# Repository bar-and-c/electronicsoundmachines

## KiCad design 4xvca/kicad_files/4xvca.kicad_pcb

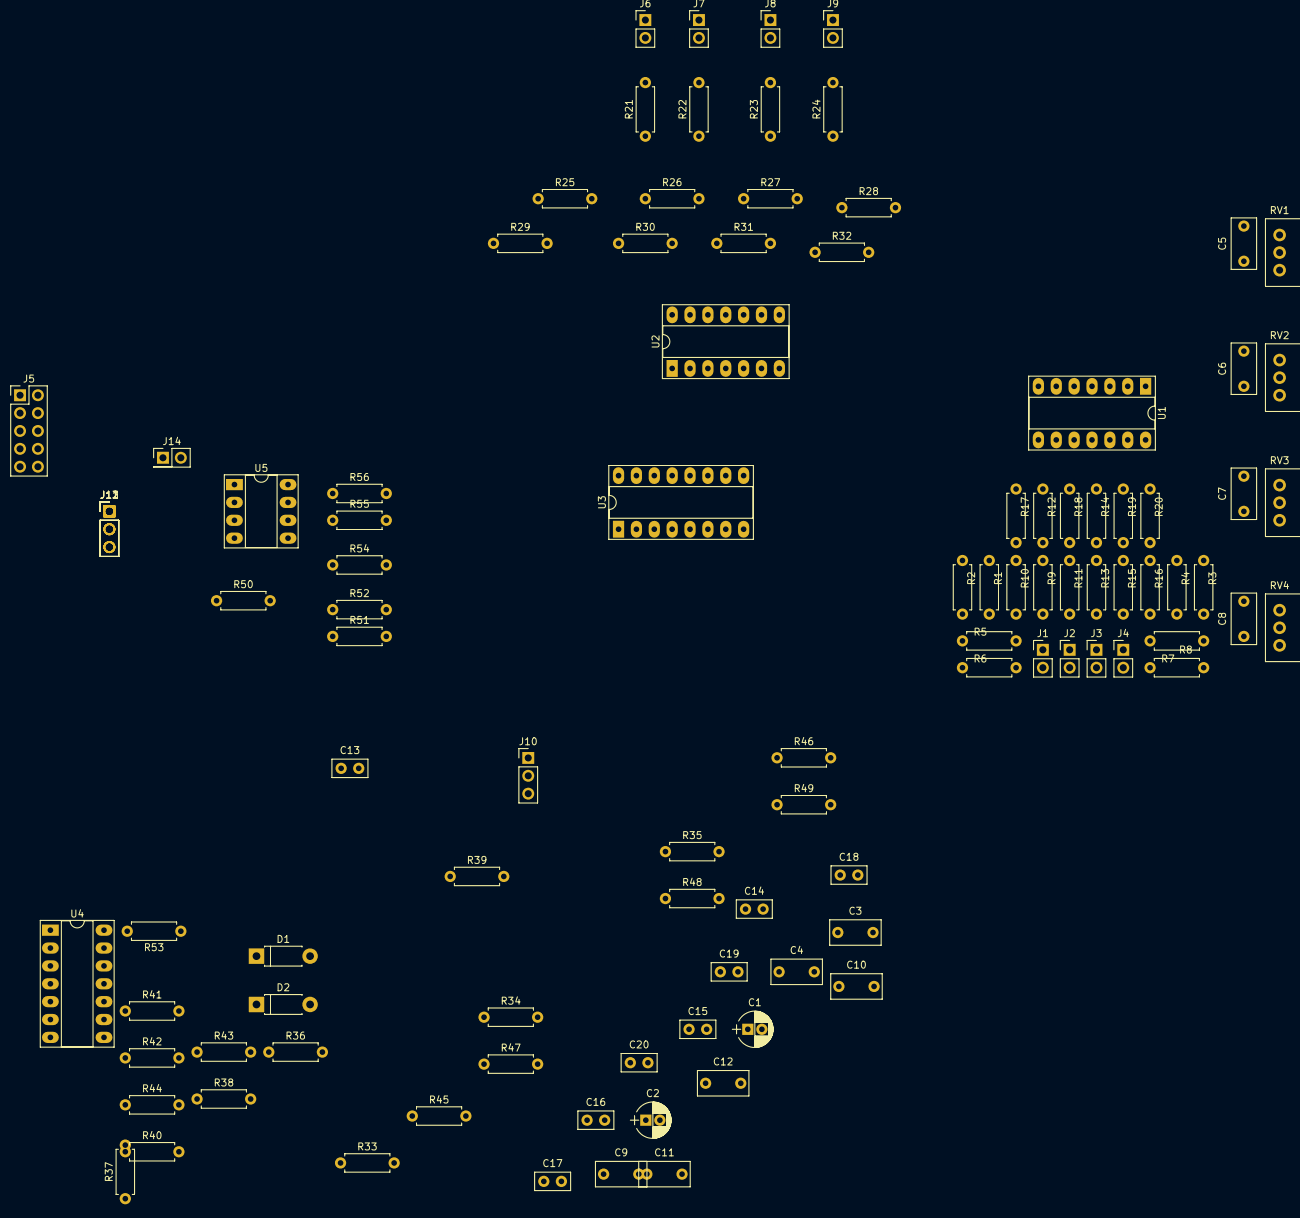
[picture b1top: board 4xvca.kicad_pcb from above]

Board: 2 copper layers, 101 parts (0 on the bottom side), 63 nets, no tracks yet.

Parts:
C1, C2: 10uF; CP_Radial_D5.0mm_P2.00mm
C3, C4, C5, C6, C7, C8, C9, C10, C11, C12: 100nF; C_Rect_L7.2mm_W3.5mm_P5.00mm_FKS2_FKP2_MKS2_MKP2
C13, C14, C15, C16: 560pF; C_Disc_D5.0mm_W2.5mm_P2.50mm
C17, C18, C19, C20: 100pF; C_Disc_D5.0mm_W2.5mm_P2.50mm
D1, D2: 1N4001; D_DO-41_SOD81_P7.62mm_Horizontal
J1: CV_1; Pin_Header_Straight_1x02_Pitch2.54mm
J2: CV_2; Pin_Header_Straight_1x02_Pitch2.54mm
J3: CV_3; Pin_Header_Straight_1x02_Pitch2.54mm
J4: CV_4; Pin_Header_Straight_1x02_Pitch2.54mm
J5: EUROPOWER; Pin_Header_Straight_2x05_Pitch2.54mm
J6: IN_1; Pin_Header_Straight_1x02_Pitch2.54mm
J7: IN_2; Pin_Header_Straight_1x02_Pitch2.54mm
J8: IN_3; Pin_Header_Straight_1x02_Pitch2.54mm
J9: IN_4; Pin_Header_Straight_1x02_Pitch2.54mm
J10: OUT_1; Pin_Header_Straight_1x03_Pitch2.54mm
J11: OUT_2; Pin_Header_Straight_1x03_Pitch2.54mm
J12: OUT_3; Pin_Header_Straight_1x03_Pitch2.54mm
J13: OUT_4; Pin_Header_Straight_1x03_Pitch2.54mm
J14: MIX_OUT; Pin_Header_Straight_2x01_Pitch2.54mm
R1, R2, R3, R4: 15k; R_Axial_DIN0207_L6.3mm_D2.5mm_P7.62mm_Horizontal
R5, R6, R7, R8: 12k; R_Axial_DIN0207_L6.3mm_D2.5mm_P7.62mm_Horizontal
R9, R10, R11, R12, R13, R14, R15, R16: 62k; R_Axial_DIN0207_L6.3mm_D2.5mm_P7.62mm_Horizontal
R17, R18, R19, R20, R21, R22, R23, R24, R25, R26, R27, R28, R40, R43, R44, R49, R54: 100k; R_Axial_DIN0207_L6.3mm_D2.5mm_P7.62mm_Horizontal
R29, R30, R31, R32, R38, R39, R41, R42: 30k; R_Axial_DIN0207_L6.3mm_D2.5mm_P7.62mm_Horizontal
R33, R34, R35, R36: 500; R_Axial_DIN0207_L6.3mm_D2.5mm_P7.62mm_Horizontal
R37: 7.5k; R_Axial_DIN0207_L6.3mm_D2.5mm_P7.62mm_Horizontal
R45, R46, R47, R48, R55: 1k; R_Axial_DIN0207_L6.3mm_D2.5mm_P7.62mm_Horizontal
R50, R51, R52, R53, R56: 100; R_Axial_DIN0207_L6.3mm_D2.5mm_P7.62mm_Horizontal
RV1, RV2, RV3, RV4: 100k; Potentiometer_Alps_RK09Y_Vertical
U1, U2, U4: TL074; DIP-14_W7.62mm_Socket_LongPads
U3: V2164M; DIP-16_W7.62mm_Socket_LongPads
U5: TL071; DIP-8_W7.62mm_Socket_LongPads

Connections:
+12V: C1.1, C3.1, C9.1, C11.1, D1.1, J5.9, J5.10, R37.1, U1.4, U2.4, U3.16, U4.4, U5.7
-12V: C2.2, C4.2, C10.2, C12.2, D2.2, J5.1, J5.2, R1.2, R2.2, R3.2, R4.2, U1.11, U2.11, U3.9, U4.11, U5.4
GND: C1.2, C2.1, C3.2, C4.1, C5.2, C6.2, C7.2, C8.2, C9.2, C10.1, C11.2, C12.1, C13.2, C14.2, C15.2, C16.2, D1.2, D2.1, J1.2, J2.2, J3.2, J4.2, J5.3, J5.4, J5.5, J5.6, J5.7, J5.8, J6.2, J7.2, J8.2, J9.2, J10.2, J11.2, J12.2, J13.2, J14.2, R5.1, R6.1, R7.1, R8.1, R45.2, R46.2, R47.2, R48.2, R55.2, RV1.3, RV2.3, RV3.3, RV4.3, U1.3, U1.5, U1.10, U1.12, U2.3, U2.5, U2.10, U2.12, U3.8, U4.3, U4.5, U4.10, U4.12, U5.3
unnamed: C5.1, RV1.2, U3.3
unnamed: C6.1, RV2.2, U3.6
unnamed: C7.1, RV3.2, U3.11
unnamed: C8.1, RV4.2, U3.14
unnamed: C13.1, R33.2
unnamed: C14.1, R34.2
unnamed: C15.1, R35.2
unnamed: C16.1, R36.2
unnamed: C17.1, R38.1, R45.1, R50.2, U4.1
unnamed: C17.2, R38.2, U3.4, U4.2
unnamed: C18.1, R39.1, R47.1, R52.2, U4.7
unnamed: C18.2, R39.2, U3.12, U4.6
unnamed: C19.1, R41.1, R46.1, R51.2, U4.8
unnamed: C19.2, R41.2, U3.5, U4.9
unnamed: C20.1, R42.1, R48.1, R53.2, U4.14
unnamed: C20.2, R42.2, U3.13, U4.13
unnamed: J1.1, R9.2
unnamed: J2.1, R11.2
unnamed: J3.1, R13.2
unnamed: J4.1, R15.2
unnamed: J6.1, R21.2
unnamed: J7.1, R22.2
unnamed: J8.1, R23.2
unnamed: J9.1, R24.2
unnamed: J10.1, R50.1
unnamed: J10.3, R40.1
unnamed: J11.1, R51.1
unnamed: J11.3, R43.1
unnamed: J12.1, R52.1
unnamed: J12.3, R44.1
unnamed: J13.1, R53.1
unnamed: J13.3, R49.1
unnamed: J14.1, R56.1
unnamed: R1.1, R5.2, R10.2
unnamed: R9.1, R10.1, R17.2, U1.2
unnamed: R11.1, R12.1, R18.2, U1.6
unnamed: R2.1, R6.2, R12.2
unnamed: R13.1, R14.1, R19.2, U1.9
unnamed: R3.1, R7.2, R14.2
unnamed: R15.1, R16.1, R20.2, U1.13
unnamed: R4.1, R8.2, R16.2
unnamed: R17.1, RV1.1, U1.1
unnamed: R18.1, RV2.1, U1.7
unnamed: R19.1, RV3.1, U1.8
unnamed: R20.1, RV4.1, U1.14
unnamed: R21.1, R25.2, U2.2
unnamed: R22.1, R26.2, U2.6
unnamed: R23.1, R27.2, U2.9
unnamed: R24.1, R28.2, U2.13
unnamed: R25.1, R29.2, U2.1
unnamed: R26.1, R30.2, U2.7
unnamed: R27.1, R31.2, U2.8
unnamed: R28.1, R32.2, U2.14
unnamed: R29.1, R33.1, U3.2
unnamed: R30.1, R34.1, U3.7
unnamed: R31.1, R35.1, U3.10
unnamed: R32.1, R36.1, U3.15
unnamed: R37.2, U3.1
unnamed: R40.2, R43.2, R44.2, R49.2, R54.2, U5.2
unnamed: R54.1, R55.1, R56.2, U5.6

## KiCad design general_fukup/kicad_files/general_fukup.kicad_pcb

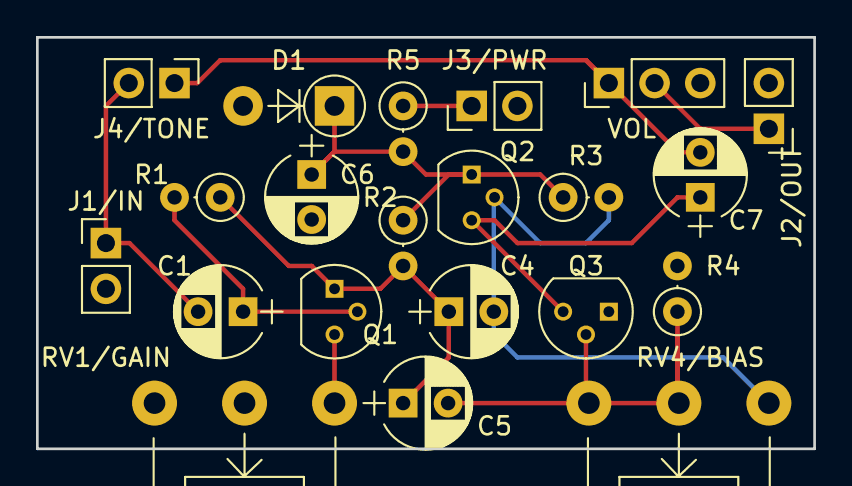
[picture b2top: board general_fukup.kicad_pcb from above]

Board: 2 copper layers, 43.2 x 22.9 mm, 21 parts (0 on the bottom side), 12 nets.

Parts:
C1: 100uF; CP_Radial_D5.0mm_P2.50mm
C4, C5, C7: 4.7 uF; CP_Radial_D5.0mm_P2.50mm
C6: 22 uF; CP_Radial_D5.0mm_P2.50mm
D1: 1N4001; D_DO-41_SOD81_P5.08mm_Vertical_AnodeUp
J1/IN: INPUT; Pin_Header_Straight_1x02_Pitch2.54mm
J2/OUT: OUTPUT; Pin_Header_Straight_1x02_Pitch2.54mm
J3/PWR: POWER; Pin_Header_Straight_1x02_Pitch2.54mm
J4/TONE: TONE; Pin_Header_Straight_1x02_Pitch2.54mm
Q1, Q2: BC337; TO-92_Molded_Narrow
Q3: BC327; TO-92_Molded_Narrow
R1: 1M; R_Axial_DIN0207_L6.3mm_D2.5mm_P2.54mm_Vertical
R2: 10k; R_Axial_DIN0207_L6.3mm_D2.5mm_P2.54mm_Vertical
R3, R4: 47k; R_Axial_DIN0207_L6.3mm_D2.5mm_P2.54mm_Vertical
R5: 150; R_Axial_DIN0207_L6.3mm_D2.5mm_P2.54mm_Vertical
RV1/GAIN, RV4/BIAS: 10k lin; Potentiometer_WirePads
VOL: 100k log; Pin_Header_Straight_1x03_Pitch2.54mm

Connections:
+9V: J3/PWR.1, R5.1
GND: C6.2, D1.2, J1/IN.2, J2/OUT.2, J3/PWR.2, Q3.1, R4.2, RV1/GAIN.2, RV1/GAIN.3, VOL.3
unnamed: C1.1, Q1.2, R1.2
unnamed: C1.2, J1/IN.1, J4/TONE.2
unnamed: C4.1, C5.1, Q1.1, R1.1, R2.2
unnamed: C4.2, Q2.2, R3.2, RV4/BIAS.1
unnamed: C5.2, Q3.2, R4.1, RV4/BIAS.2, RV4/BIAS.3
unnamed: C6.1, D1.1, Q2.1, R2.1, R3.1, R5.2
unnamed: C7.1, Q2.3, Q3.3
unnamed: C7.2, J4/TONE.1, VOL.1
unnamed: J2/OUT.1, VOL.2
unnamed: Q1.3, RV1/GAIN.1

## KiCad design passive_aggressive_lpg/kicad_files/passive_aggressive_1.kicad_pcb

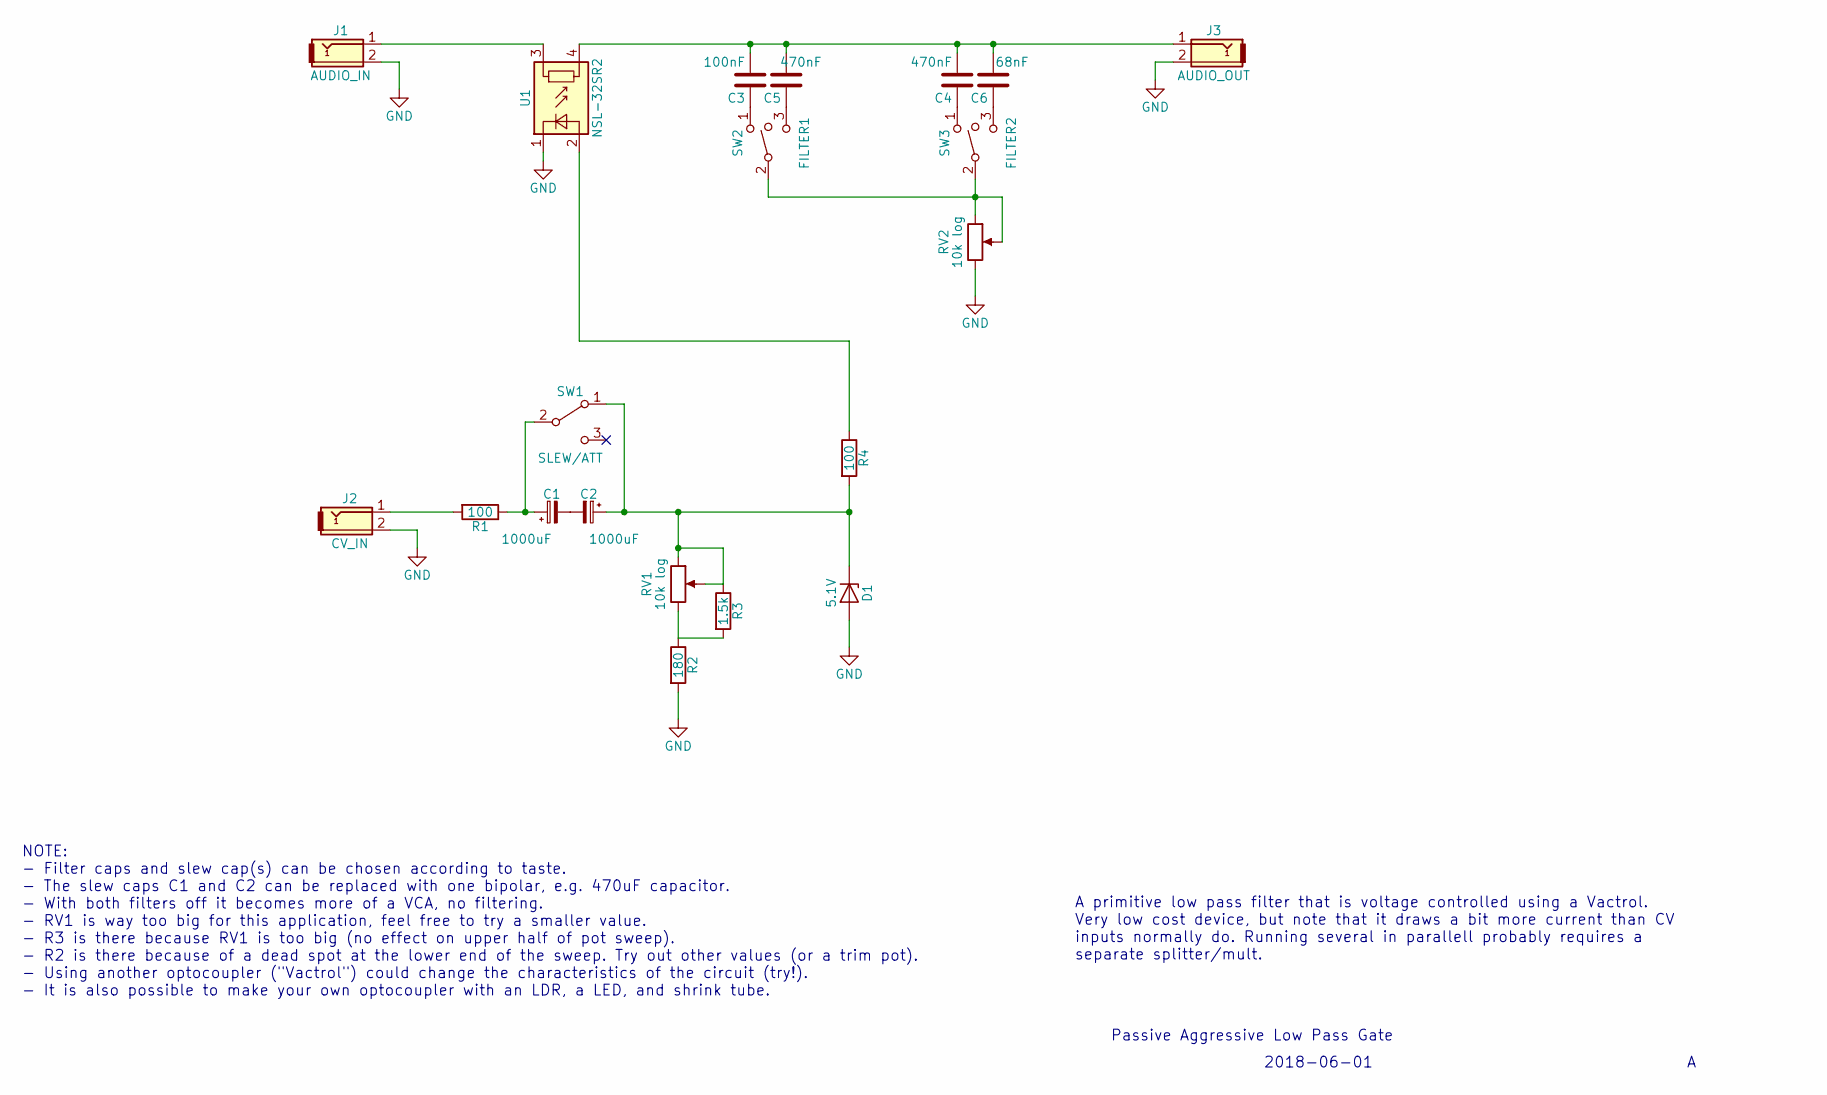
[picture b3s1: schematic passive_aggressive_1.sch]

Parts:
C1, C2: 1000uF; CP_Radial_D10.0mm_P5.00mm
C3: 100nF; C_Rect_L7.2mm_W3.5mm_P5.00mm_FKS2_FKP2_MKS2_MKP2
C4, C5: 470nF; C_Rect_L7.2mm_W3.5mm_P5.00mm_FKS2_FKP2_MKS2_MKP2
C6: 68nF; C_Rect_L7.2mm_W3.5mm_P5.00mm_FKS2_FKP2_MKS2_MKP2
D1: 5.1V; D_DO-35_SOD27_P7.62mm_Horizontal
J1: AUDIO_IN; Pin_Header_Straight_1x02_Pitch2.54mm
J2: CV_IN; Pin_Header_Straight_1x02_Pitch2.54mm
J3: AUDIO_OUT; Pin_Header_Straight_1x02_Pitch2.54mm
R1, R4: 100; R_Axial_DIN0207_L6.3mm_D2.5mm_P7.62mm_Horizontal
R2: 180; R_Axial_DIN0207_L6.3mm_D2.5mm_P7.62mm_Horizontal
R3: 1.5k; R_Axial_DIN0207_L6.3mm_D2.5mm_P7.62mm_Horizontal
RV1, RV2: 10k log; Potentiometer_Alps_RK097_Single_Vertical
SW1: SLEW/ATT; Pin_Header_Straight_1x02_Pitch2.54mm
SW2: FILTER1; Pin_Header_Straight_1x03_Pitch2.54mm
SW3: FILTER2; Pin_Header_Straight_1x03_Pitch2.54mm
U1: NSL-32SR2; Optoisolator_VTL5C

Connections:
GND: D1.2 (A), J1.2, J2.2, J3.2, R2.2, RV2.3, U1.1 (-)
unnamed: C1.1, R1.1, SW1.2 (B)
unnamed: C1.2, C2.2
unnamed: C2.1, D1.1 (K), R3.1, R4.2, RV1.1, RV1.2, SW1.1 (A)
unnamed: C3.1, SW2.1
unnamed: C3.2, C4.2, C5.2, C6.2, J3.1, U1.4
unnamed: C4.1, SW3.1
unnamed: C5.1, SW2.3
unnamed: C6.1, SW3.3
unnamed: J1.1, U1.3
unnamed: J2.1, R1.2
unnamed: R2.1, R3.2, RV1.3
unnamed: R4.1, U1.2 (+)
unnamed: RV2.1, RV2.2, SW2.2, SW3.2

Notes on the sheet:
Passive Aggressive Low Pass Gate
2018-06-01
NOTE: - Filter caps and slew cap(s) can be chosen according to taste. - The slew caps C1 and C2 can be replaced with one bipolar, e.g. 470uF capacitor. - With both filters off it becomes more of a VCA, no filtering. - RV1 is way too big for this application, feel free to try a smaller value. - R3 i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
A primitive low pass filter that is voltage controlled using a Vactrol. Very low cost device, but note that it draws a bit more current than CV inputs normally do. Running several in parallell probably requires a separate splitter/mult.

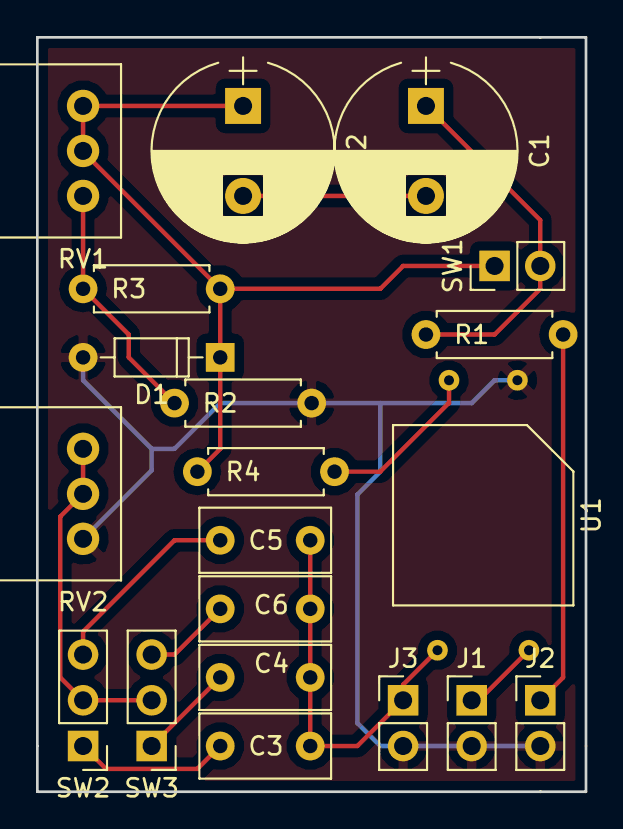
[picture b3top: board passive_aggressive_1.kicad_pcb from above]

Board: 2 copper layers, 30.5 x 41.9 mm, 20 parts (0 on the bottom side), 14 nets.

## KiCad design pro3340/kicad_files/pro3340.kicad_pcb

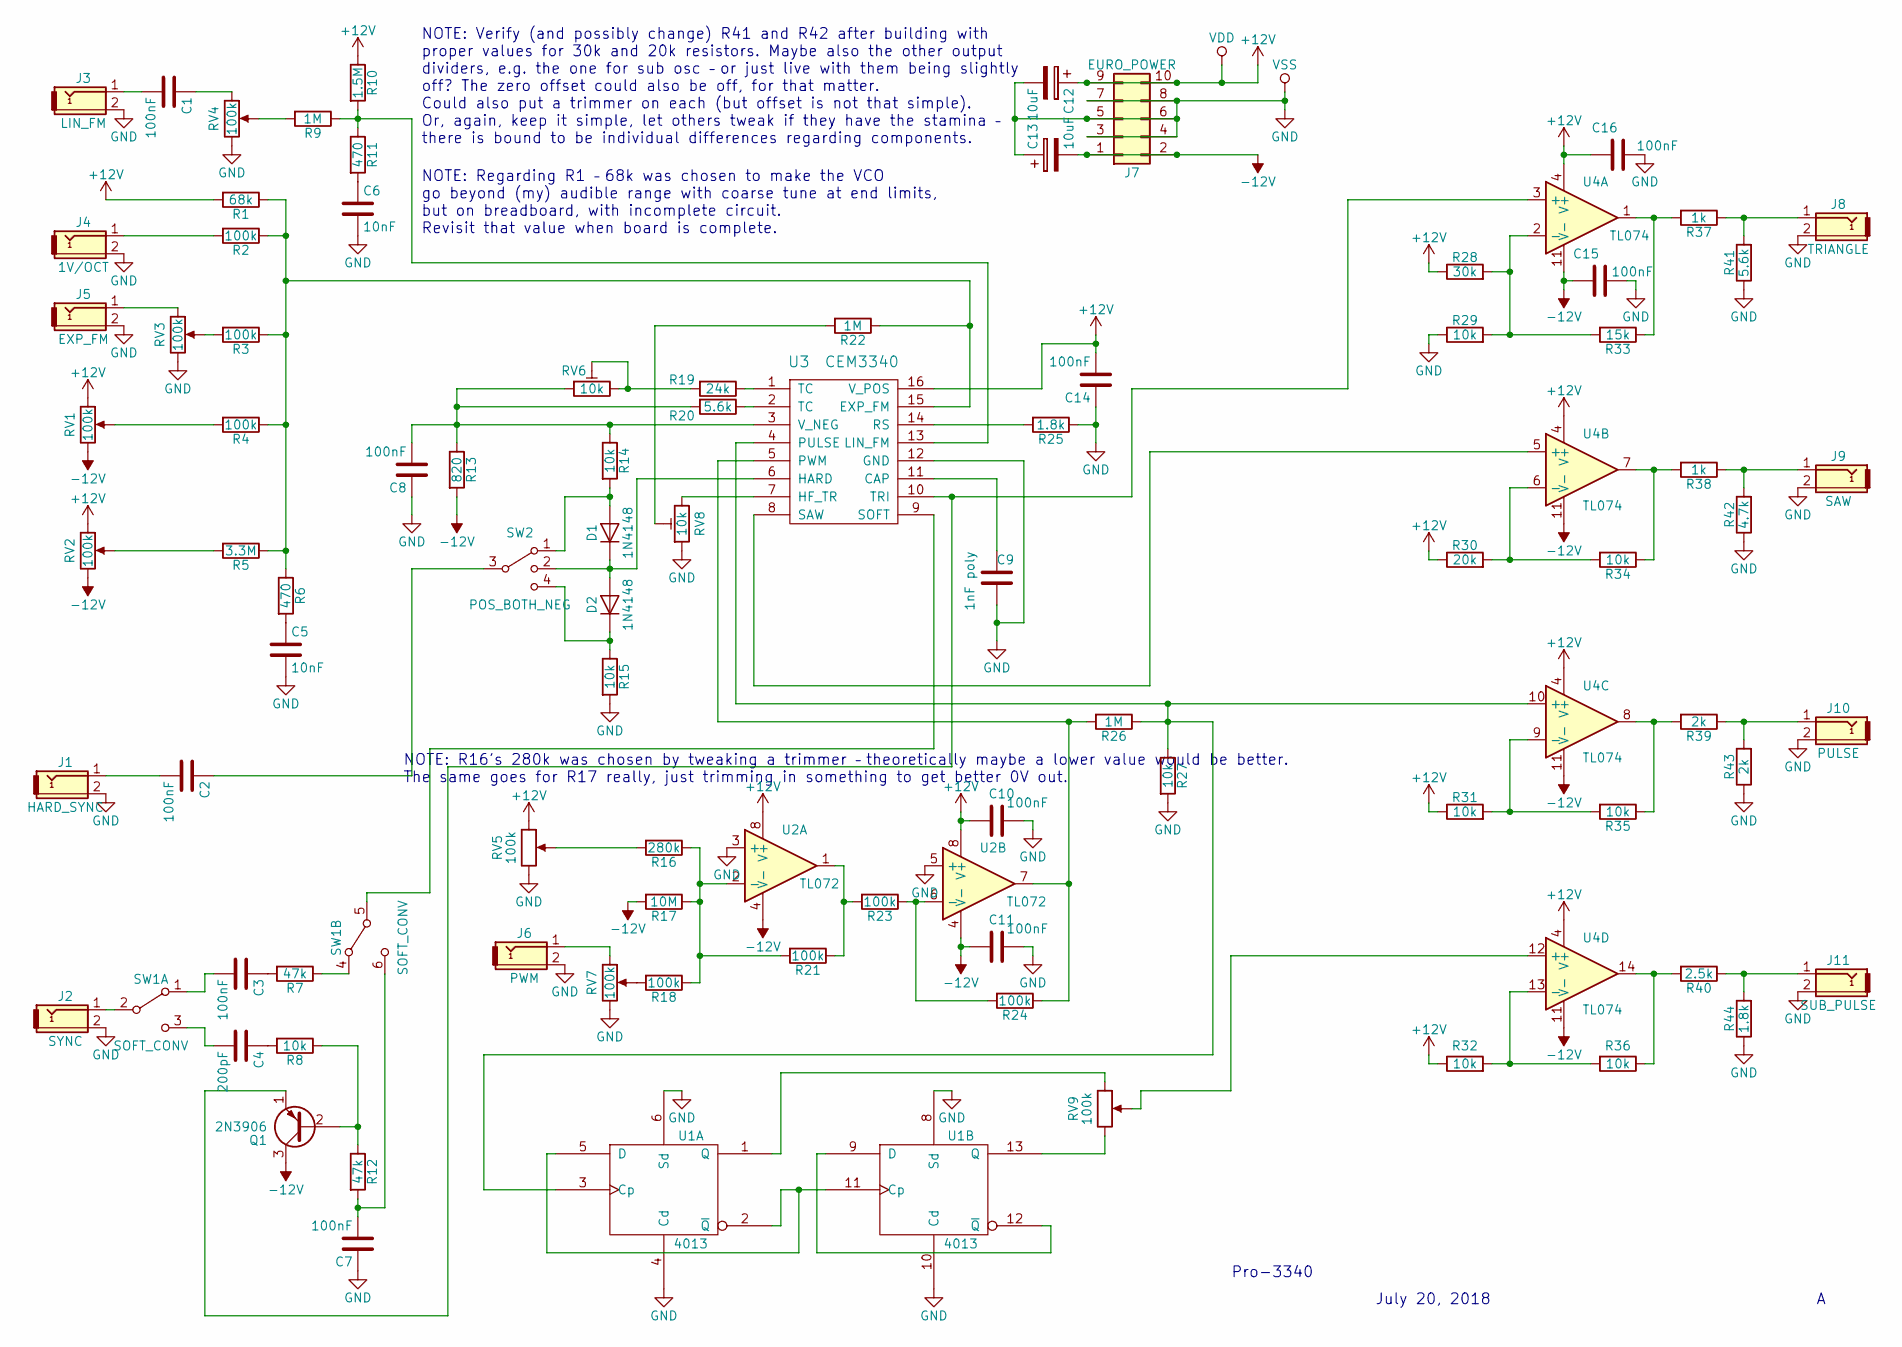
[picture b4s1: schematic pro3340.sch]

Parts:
C1, C2, C3, C7, C8, C10, C11, C14, C15, C16: 100nF; C_Rect_L7.0mm_W3.5mm_P5.00mm
C4: 200pF; C_Rect_L7.0mm_W3.5mm_P5.00mm
C5, C6: 10nF; C_Rect_L7.0mm_W3.5mm_P5.00mm
C9: 1nF poly; C_Axial_L12.0mm_D6.5mm_P15.00mm_Horizontal
C12, C13: 10uF; CP_Radial_D5.0mm_P2.50mm
D1, D2: 1N4148; D_DO-35_SOD27_P7.62mm_Horizontal
J1: HARD_SYNC; Pin_Header_Straight_1x02_Pitch2.54mm
J2: SYNC; Pin_Header_Straight_1x02_Pitch2.54mm
J3: LIN_FM; Pin_Header_Straight_1x02_Pitch2.54mm
J4: 1V/OCT; Pin_Header_Straight_1x02_Pitch2.54mm
J5: EXP_FM; Pin_Header_Straight_1x02_Pitch2.54mm
J6: PWM; Pin_Header_Straight_1x02_Pitch2.54mm
J7: EURO_POWER; Pin_Header_Straight_2x05_Pitch2.54mm
J8: TRIANGLE; Pin_Header_Straight_1x02_Pitch2.54mm
J9: SAW; Pin_Header_Straight_1x02_Pitch2.54mm
J10: PULSE; Pin_Header_Straight_1x02_Pitch2.54mm
J11: SUB_PULSE; Pin_Header_Straight_1x02_Pitch2.54mm
Q1: 2N3906; TO-92_Inline_Wide
R1: 68k; R_Axial_DIN0207_L6.3mm_D2.5mm_P7.62mm_Horizontal
R2, R3, R4, R18, R21, R23, R24: 100k; R_Axial_DIN0207_L6.3mm_D2.5mm_P7.62mm_Horizontal
R5: 3.3M; R_Axial_DIN0207_L6.3mm_D2.5mm_P7.62mm_Horizontal
R6, R11: 470; R_Axial_DIN0207_L6.3mm_D2.5mm_P7.62mm_Horizontal
R7, R12: 47k; R_Axial_DIN0207_L6.3mm_D2.5mm_P7.62mm_Horizontal
R8, R14, R15, R27, R29, R31, R32, R34, R35, R36: 10k; R_Axial_DIN0207_L6.3mm_D2.5mm_P7.62mm_Horizontal
R9, R22, R26: 1M; R_Axial_DIN0207_L6.3mm_D2.5mm_P7.62mm_Horizontal
R10: 1.5M; R_Axial_DIN0207_L6.3mm_D2.5mm_P7.62mm_Horizontal
R13: 820; R_Axial_DIN0207_L6.3mm_D2.5mm_P7.62mm_Horizontal
R16: 280k; R_Axial_DIN0207_L6.3mm_D2.5mm_P7.62mm_Horizontal
R17: 10M; R_Axial_DIN0207_L6.3mm_D2.5mm_P7.62mm_Horizontal
R19: 24k; R_Axial_DIN0207_L6.3mm_D2.5mm_P7.62mm_Horizontal
R20, R41: 5.6k; R_Axial_DIN0207_L6.3mm_D2.5mm_P7.62mm_Horizontal
R25, R44: 1.8k; R_Axial_DIN0207_L6.3mm_D2.5mm_P7.62mm_Horizontal
R28: 30k; R_Axial_DIN0207_L6.3mm_D2.5mm_P7.62mm_Horizontal
R30: 20k; R_Axial_DIN0207_L6.3mm_D2.5mm_P7.62mm_Horizontal
R33: 15k; R_Axial_DIN0207_L6.3mm_D2.5mm_P7.62mm_Horizontal
R37, R38: 1k; R_Axial_DIN0207_L6.3mm_D2.5mm_P7.62mm_Horizontal
R39, R43: 2k; R_Axial_DIN0207_L6.3mm_D2.5mm_P7.62mm_Horizontal
R40: 2.5k; R_Axial_DIN0207_L6.3mm_D2.5mm_P7.62mm_Horizontal
R42: 4.7k; R_Axial_DIN0207_L6.3mm_D2.5mm_P7.62mm_Horizontal
RV1, RV2, RV3, RV4, RV5, RV7: 100k; Potentiometer_Alps_RK09Y_Vertical
RV6, RV8: 10k; Potentiometer_Trimmer_Bourns_3266Y
RV9: 100k; Pin_Header_Straight_1x03_Pitch2.54mm
SW1: SOFT_CONV; Pin_Header_Straight_1x06_Pitch2.54mm
SW2: POS_BOTH_NEG; Pin_Header_Straight_1x04_Pitch2.54mm
U1: 4013; DIP-14_W10.16mm_LongPads
U2: TL072; DIP-8_W10.16mm_LongPads
U3: CEM3340; DIP-16_W10.16mm_LongPads
U4: TL074; DIP-14_W10.16mm_LongPads

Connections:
+12V: C10.2, C12.1, C14.2, C16.2, J7.9, J7.10, R1.2, R10.1, R28.1, R30.1, R31.1, R32.1, RV1.1, RV2.1, RV5.1, U1.14 (VDD), U2.8 (V+), U3.16 (V_POS), U4.4 (V+)
-12V: C11.2, C13.2, C15.1, J7.1, J7.2, Q1.3 (C), R13.2, R17.2, RV1.3, RV2.3, U2.4 (V-), U4.11 (V-)
GND: C5.2, C6.2, C7.1, C8.1, C9.1, C10.1, C11.1, C12.2, C13.1, C14.1, C15.2, C16.1, J1.2, J2.2, J3.2, J4.2, J5.2, J6.2, J7.3, J7.4, J7.5, J7.6, J7.7, J7.8, J8.2, J9.2, J10.2, J11.2, R15.2, R25.1, R27.2, R29.1, R41.1, R42.1, R43.1, R44.1, RV3.3, RV4.3, RV5.3, RV7.3, RV8.1, U1.4 (Cd), U1.6 (Sd), U1.7 (VSS), U1.8 (Sd), U1.10 (Cd), U2.3 (+), U2.5 (+), U3.12 (GND)
unnamed: C1.1, RV4.1
unnamed: C1.2, J3.1
unnamed: C2.1, SW2.3
unnamed: C2.2, J1.1
unnamed: C3.1, R7.2
unnamed: C3.2, SW1.1 (A)
unnamed: C4.1, R8.2
unnamed: C4.2, SW1.3 (C)
unnamed: C5.1, R6.2
unnamed: C6.1, R11.2
unnamed: C7.2, R12.2, SW1.6 (C)
unnamed: C8.2, R13.1, R14.1, R20.2, RV6.1, U3.3 (V_NEG)
unnamed: C9.2, U3.11 (CAP)
unnamed: D1.1 (K), D2.2 (A), SW2.2, U3.6 (HARD)
unnamed: D1.2 (A), R14.2, SW2.1
unnamed: D2.1 (K), R15.1, SW2.4
unnamed: J2.1, SW1.2 (B)
unnamed: J4.1, R2.2
unnamed: J5.1, RV3.1
unnamed: J6.1, RV7.1
unnamed: J8.1, R37.1, R41.2
unnamed: J9.1, R38.1, R42.2
unnamed: J10.1, R39.1, R43.2
unnamed: J11.1, R40.1, R44.2
unnamed: Q1.1 (E), U3.10 (TRI), U4.3 (+)
unnamed: Q1.2 (B), R8.1, R12.1
unnamed: R1.1, R2.1, R3.1, R4.1, R5.1, R6.1, R22.1, U3.15 (EXP_FM)
unnamed: R3.2, RV3.2
unnamed: R4.2, RV1.2
unnamed: R5.2, RV2.2
unnamed: R7.1, SW1.4 (A)
unnamed: R9.2, RV4.2
unnamed: R9.1, R10.2, R11.1, U3.13 (LIN_FM)
unnamed: R16.1, R17.1, R18.1, R21.2, U2.2 (-)
unnamed: R16.2, RV5.2
unnamed: R18.2, RV7.2
unnamed: R19.1, U3.1 (TC)
unnamed: R19.2, RV6.2, RV6.3
unnamed: R20.1, U3.2 (TC)
unnamed: R21.1, R23.2, U2.1
unnamed: R22.2, RV8.2
unnamed: R23.1, R24.2, U2.6 (-)
unnamed: R24.1, R26.2, U2.7, U3.5 (PWM)
unnamed: R25.2, U3.14 (RS)
unnamed: R26.1, R27.1, U1.3 (Cp), U3.4 (PULSE), U4.10 (+)
unnamed: R28.2, R29.2, R33.2, U4.2 (-)
unnamed: R30.2, R34.2, U4.6 (-)
unnamed: R31.2, R35.2, U4.9 (-)
unnamed: R32.2, R36.2, U4.13 (-)
unnamed: R33.1, R37.2, U4.1
unnamed: R34.1, R38.2, U4.7
unnamed: R35.1, R39.2, U4.8
unnamed: R36.1, R40.2, U4.14
unnamed: RV8.3, U3.7 (HF_TR)
unnamed: RV9.1, U1.1 (Q)
unnamed: RV9.2, U4.12 (+)
unnamed: RV9.3, U1.13 (Q)
unnamed: SW1.5 (B), U3.9 (SOFT)
unnamed: U1.2 (~Q), U1.5 (D), U1.11 (Cp)
unnamed: U1.9 (D), U1.12 (~Q)
unnamed: U3.8 (SAW), U4.5 (+)

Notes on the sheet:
NOTE: Regarding R1 – 68k was chosen to make the VCO go beyond (my) audible range with coarse tune at end limits, but on breadboard, with incomplete circuit. Revisit that value when board is complete.
NOTE: Verify (and possibly change) R41 and R42 after building with proper values for 30k and 20k resistors. Maybe also the other output dividers, e.g. the one for sub osc – or just live with them being slightly off? The zero offset could also be off, for that matter. Could also put a trimmer on eac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
Pro-3340
July 20, 2018
NOTE: R16's 280k was chosen by tweaking a trimmer – theoretically maybe a lower value would be better. The same goes for R17 really, just trimming in something to get better 0V out.

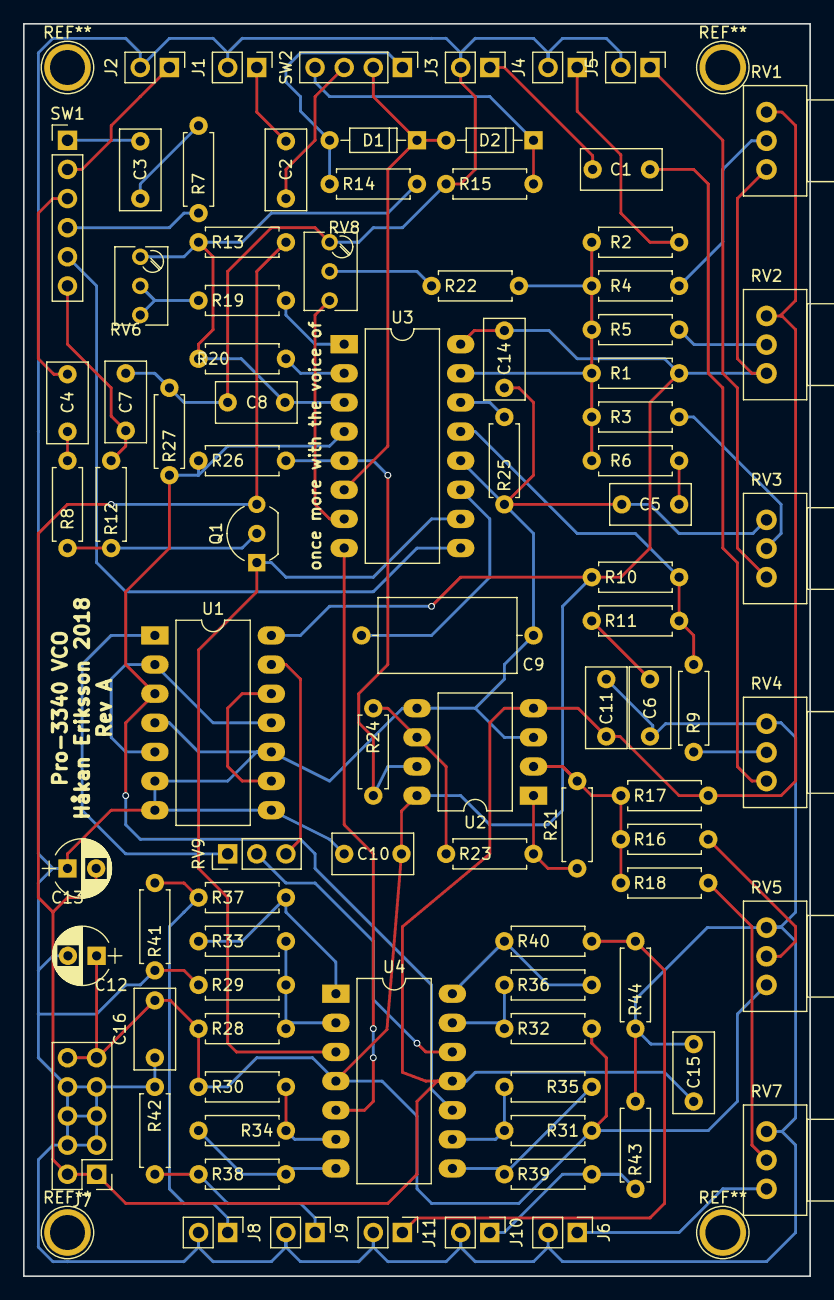
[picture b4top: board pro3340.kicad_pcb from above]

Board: 2 copper layers, 68.6 x 109.2 mm, 89 parts (0 on the bottom side), 64 nets.

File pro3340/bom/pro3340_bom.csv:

"Source:","/Users/hakan/kod/electronics/pro3340/kicad_files/pro3340.sch"
"Date:","Söndag 19 Augusti 2018 22:09:32"
"Tool:","Eeschema 4.0.7"
"Generator:","bom_csv_grouped_by_value.py"
"Component Count:","89"

"Collated Components:"

"Item","Qty","Reference(s)","Value","LibPart","Footprint","Datasheet"
"1","10","C1, C2, C3, C7, C8, C10, C11, C14, C15, C16","100nF","device:C","Capacitors_THT:C_Rect_L7.0mm_W3.5mm_P5.00mm",""
"2","1","C4","200pF","device:C","Capacitors_THT:C_Rect_L7.0mm_W3.5mm_P5.00mm",""
"3","2","C5, C6","10nF","device:C","Capacitors_THT:C_Rect_L7.0mm_W3.5mm_P5.00mm",""
"4","1","C9","1nF poly","device:C","Capacitors_THT:C_Axial_L12.0mm_D6.5mm_P15.00mm_Horizontal",""
"5","2","C12, C13","10uF","device:CP","Capacitors_THT:CP_Radial_D5.0mm_P2.50mm",""
"6","2","D1, D2","1N4148","diode:1N4148","Diodes_THT:D_DO-35_SOD27_P7.62mm_Horizontal",""
"7","1","J1","HARD_SYNC","conn:Audio-Jack-2","Pin_Headers:Pin_Header_Straight_1x02_Pitch2.54mm",""
"8","1","J2","SYNC","conn:Audio-Jack-2","Pin_Headers:Pin_Header_Straight_1x02_Pitch2.54mm",""
"9","1","J3","LIN_FM","conn:Audio-Jack-2","Pin_Headers:Pin_Header_Straight_1x02_Pitch2.54mm",""
"10","1","J4","1V/OCT","conn:Audio-Jack-2","Pin_Headers:Pin_Header_Straight_1x02_Pitch2.54mm",""
"11","1","J5","EXP_FM","conn:Audio-Jack-2","Pin_Headers:Pin_Header_Straight_1x02_Pitch2.54mm",""
"12","1","J6","PWM","conn:Audio-Jack-2","Pin_Headers:Pin_Header_Straight_1x02_Pitch2.54mm",""
"13","1","J7","EURO_POWER","conn:Conn_02x05_Odd_Even","Pin_Headers:Pin_Header_Straight_2x05_Pitch2.54mm",""
"14","1","J8","TRIANGLE","conn:Audio-Jack-2","Pin_Headers:Pin_Header_Straight_1x02_Pitch2.54mm",""
"15","1","J9","SAW","conn:Audio-Jack-2","Pin_Headers:Pin_Header_Straight_1x02_Pitch2.54mm",""
"16","1","J10","PULSE","conn:Audio-Jack-2","Pin_Headers:Pin_Header_Straight_1x02_Pitch2.54mm",""
"17","1","J11","SUB_PULSE","conn:Audio-Jack-2","Pin_Headers:Pin_Header_Straight_1x02_Pitch2.54mm",""
"18","1","Q1","2N3906","transistors:2N3906","TO_SOT_Packages_THT:TO-92_Inline_Wide",""
"19","1","R1","68k","device:R","Resistors_THT:R_Axial_DIN0207_L6.3mm_D2.5mm_P7.62mm_Horizontal",""
"20","7","R2, R3, R4, R18, R21, R23, R24","100k","device:R","Resistors_THT:R_Axial_DIN0207_L6.3mm_D2.5mm_P7.62mm_Horizontal",""
"21","1","R5","3.3M","device:R","Resistors_THT:R_Axial_DIN0207_L6.3mm_D2.5mm_P7.62mm_Horizontal",""
"22","2","R6, R11","470","device:R","Resistors_THT:R_Axial_DIN0207_L6.3mm_D2.5mm_P7.62mm_Horizontal",""
"23","2","R7, R12","47k","device:R","Resistors_THT:R_Axial_DIN0207_L6.3mm_D2.5mm_P7.62mm_Horizontal",""
"24","10","R8, R14, R15, R27, R29, R31, R32, R34, R35, R36","10k","device:R","Resistors_THT:R_Axial_DIN0207_L6.3mm_D2.5mm_P7.62mm_Horizontal",""
"25","3","R9, R22, R26","1M","device:R","Resistors_THT:R_Axial_DIN0207_L6.3mm_D2.5mm_P7.62mm_Horizontal",""
"26","1","R10","1.5M","device:R","Resistors_THT:R_Axial_DIN0207_L6.3mm_D2.5mm_P7.62mm_Horizontal",""
"27","1","R13","820","device:R","Resistors_THT:R_Axial_DIN0207_L6.3mm_D2.5mm_P7.62mm_Horizontal",""
"28","1","R16","280k","device:R","Resistors_THT:R_Axial_DIN0207_L6.3mm_D2.5mm_P7.62mm_Horizontal",""
"29","1","R17","10M","device:R","Resistors_THT:R_Axial_DIN0207_L6.3mm_D2.5mm_P7.62mm_Horizontal",""
"30","1","R19","24k","device:R","Resistors_THT:R_Axial_DIN0207_L6.3mm_D2.5mm_P7.62mm_Horizontal",""
"31","2","R20, R41","5.6k","device:R","Resistors_THT:R_Axial_DIN0207_L6.3mm_D2.5mm_P7.62mm_Horizontal",""
"32","2","R25, R44","1.8k","device:R","Resistors_THT:R_Axial_DIN0207_L6.3mm_D2.5mm_P7.62mm_Horizontal",""
"33","1","R28","30k","device:R","Resistors_THT:R_Axial_DIN0207_L6.3mm_D2.5mm_P7.62mm_Horizontal",""
"34","1","R30","20k","device:R","Resistors_THT:R_Axial_DIN0207_L6.3mm_D2.5mm_P7.62mm_Horizontal",""
"35","1","R33","15k","device:R","Resistors_THT:R_Axial_DIN0207_L6.3mm_D2.5mm_P7.62mm_Horizontal",""
"36","2","R37, R38","1k","device:R","Resistors_THT:R_Axial_DIN0207_L6.3mm_D2.5mm_P7.62mm_Horizontal",""
"37","2","R39, R43","2k","device:R","Resistors_THT:R_Axial_DIN0207_L6.3mm_D2.5mm_P7.62mm_Horizontal",""
"38","1","R40","2.5k","device:R","Resistors_THT:R_Axial_DIN0207_L6.3mm_D2.5mm_P7.62mm_Horizontal",""
"39","1","R42","4.7k","device:R","Resistors_THT:R_Axial_DIN0207_L6.3mm_D2.5mm_P7.62mm_Horizontal",""
"40","6","RV1, RV2, RV3, RV4, RV5, RV7","100k","device:POT","Potentiometers:Potentiometer_Alps_RK09Y_Vertical",""
"41","2","RV6, RV8","10k","device:POT_TRIM","Potentiometers:Potentiometer_Trimmer_Bourns_3266Y",""
"42","1","RV9","100k","device:POT","Pin_Headers:Pin_Header_Straight_1x03_Pitch2.54mm",""
"43","1","SW1","SOFT_CONV","switches:SW_DPDT_x2","Pin_Headers:Pin_Header_Straight_1x06_Pitch2.54mm",""
"44","1","SW2","POS_BOTH_NEG","switches:SW_SP3T","Pin_Headers:Pin_Header_Straight_1x04_Pitch2.54mm",""
"45","1","U1","4013","cmos4000:4013","Housings_DIP:DIP-14_W10.16mm_LongPads",""
"46","1","U2","TL072","linear:TL072","Housings_DIP:DIP-8_W10.16mm_LongPads",""
"47","1","U3","CEM3340","hakane:CEM3340","Housings_DIP:DIP-16_W10.16mm_LongPads",""
"48","1","U4","TL074","linear:TL074","Housings_DIP:DIP-14_W10.16mm_LongPads",""
